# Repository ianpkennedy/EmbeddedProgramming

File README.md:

## Embedded Programming

In this repo, there are a variety of embedded programming assignments of varying difficulty using MCUs from the PIC32 family, written primarily in C with some supporting python scripts. I am particularly proud of the "Motor Control" project using nested control loops to control a electric motor over various trajectories.

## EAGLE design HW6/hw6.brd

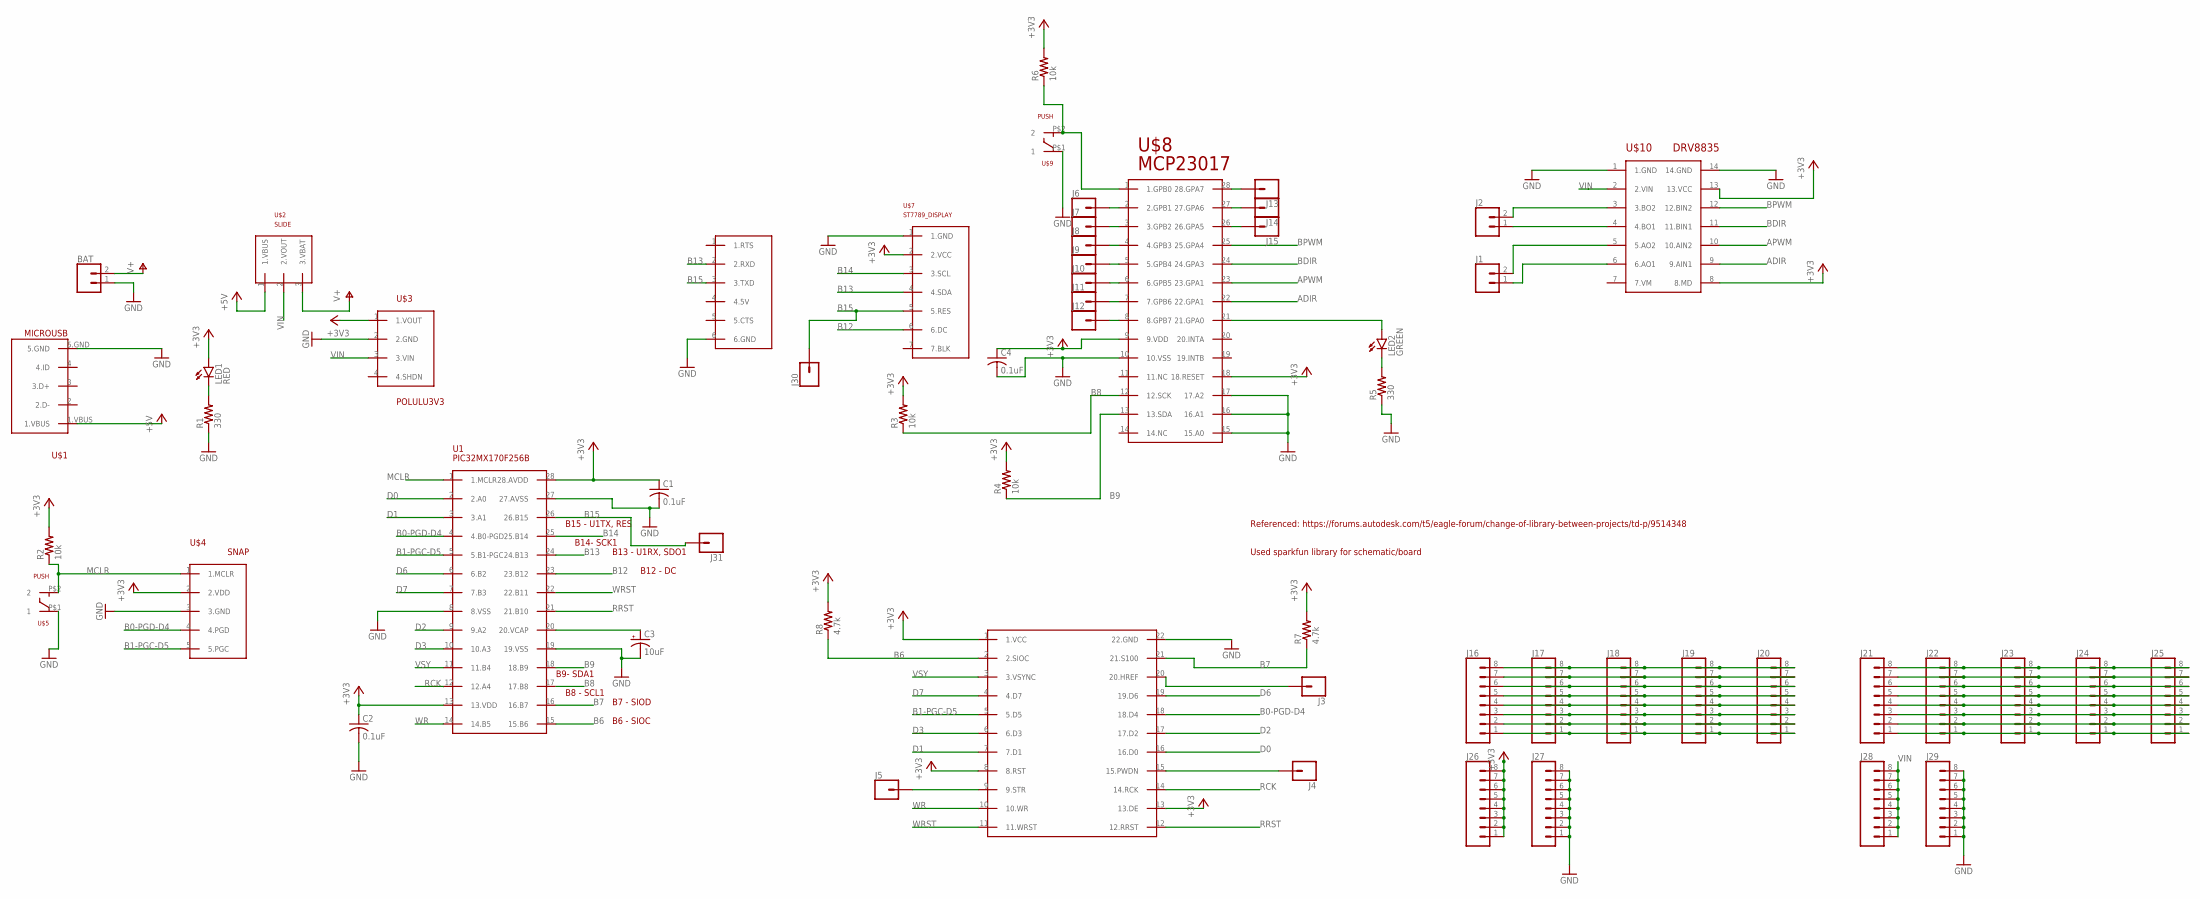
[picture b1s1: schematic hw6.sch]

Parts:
BAT: CONN_02; 1X02
C1, C2, C4: 0.1uF; C025-030X050
C3: 10uF; B45181B
J1, J2: CONN_02; 1X02
J3, J4, J5, J6, J7, J8, J9, J10, J11, J12, J13, J14, J15, J30, J31: CONN_01; 1X01
J16, J17, J18, J19, J20, J21, J22, J23, J24, J25, J26, J27, J28, J29: CONN_08"; 1X08
LED1: RED; LED3MM
LED2: GREEN; LED3MM
R1, R5: 330; 0207/10
R2, R3, R4, R6: 10k; 0207/10
R7, R8: 4.7k; 0207/10
U1: PIC32MX170F256B; DIL28-3
U$1: MICROUSB; MICROUSB1
U$2: SLIDE
U$3: POLULU3V3
U$4: SNAP
U$5, U$9: PUSH
U$6: USB2UART
U$7: ST7789_DISPLAY
U$8: MCP23017
U$10: DRV8835
U$11: OV7670_CAMERA; OV7870_CAMERA

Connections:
+3V3: C1.1, C2.1, C4.1, J26.1, J26.2, J26.3, J26.4, J26.5, J26.6, J26.7, J26.8, LED1.A, R2.2, R3.2, R4.2, R6.2, R7.2, R8.2, U1.13 (13.VDD), U1.28 (28.AVDD), U$3.1 (1.VOUT), U$4.2 (2.VDD), U$7.2 (2.VCC), U$8.9 (9.VDD), U$8.18 (18.RESET), U$10.8 (8.MD), U$10.13 (13.VCC), U$11.1 (1.VCC), U$11.8 (8.RST), U$11.13 (13.DE)
+5V: U$1.1.VBUS, U$2.1 (1.VBUS)
ADIR: U$8.22 (22.GPA1), U$10.9 (9.AIN1)
APWM: U$8.23 (23.GPA1), U$10.10 (10.AIN2)
B0-PGD-D4: U1.4 (4.B0-PGD), U$4.4 (4.PGD), U$11.18 (18.D4)
B1-PGC-D5: U1.5 (5.B1-PGC), U$4.5 (5.PGC), U$11.5 (5.D5)
B6: R8.1, U1.15 (15.B6), U$11.2 (2.SIOC)
B7: R7.1, U1.16 (16.B7), U$11.21 (21.S100)
B8: R3.1, U1.17 (17.B8), U$8.12 (12.SCK)
B9: R4.1, U1.18 (18.B9), U$8.13 (13.SDA)
B12: U1.23 (23.B12), U$7.6 (6.DC)
B13: U1.24 (24.B13), U$6.2 (2.RXD), U$7.4 (4.SDA)
B14: U1.25 (25.B14), U$7.3 (3.SCL)
B15: J30.1, J31.1, U1.26 (26.B15), U$6.3 (3.TXD), U$7.5 (5.RES)
BDIR: U$8.24 (24.GPA3), U$10.11 (11.BIN1)
BPWM: U$8.25 (25.GPA4), U$10.12 (12.BIN2)
D0: U1.2 (2.A0), U$11.16 (16.D0)
D1: U1.3 (3.A1), U$11.7 (7.D1)
D2: U1.9 (9.A2), U$11.17 (17.D2)
D3: U1.10 (10.A3), U$11.6 (6.D3)
D6: U1.6 (6.B2), U$11.19 (19.D6)
D7: U1.7 (7.B3), U$11.4 (4.D7)
GND: BAT.1, C1.2, C2.2, C3.-, C4.2, J27.1, J27.2, J27.3, J27.4, J27.5, J27.6, J27.7, J27.8, J29.1, J29.2, J29.3, J29.4, J29.5, J29.6, J29.7, J29.8, R1.1, R5.1, U1.8 (8.VSS), U1.19 (19.VSS), U1.27 (27.AVSS), U$1.5.GND, U$3.2 (2.GND), U$4.3 (3.GND), U$5.P$1 (1), U$6.6 (6.GND), U$7.1 (1.GND), U$8.10 (10.VSS), U$8.15 (15.A0), U$8.16 (16.A1), U$8.17 (17.A2), U$9.P$1 (1), U$10.1 (1.GND), U$10.14 (14.GND), U$11.22 (22.GND)
MCLR: R2.1, U1.1 (1.MCLR), U$4.1 (1.MCLR), U$5.P$2 (2)
unnamed: LED1.K (C), R1.2
unnamed: C3.+, U1.20 (20.VCAP)
unnamed: LED2.K (C), R5.2
unnamed: R6.1, U$8.1 (1.GPB0), U$9.P$2 (2)
unnamed: J2.2, U$10.3 (3.BO2)
unnamed: LED2.A, U$8.21 (21.GPA0)
unnamed: J2.1, U$10.4 (4.BO1)
unnamed: J1.2, U$10.5 (5.AO2)
unnamed: J1.1, U$10.6 (6.AO1)
unnamed: J5.1, U$11.9 (9.STR)
unnamed: J4.1, U$11.15 (15.PWDN)
unnamed: J3.1, U$11.20 (20.HREF)
unnamed: J6.1, U$8.2 (2.GPB1)
unnamed: J7.1, U$8.3 (3.GPB2)
unnamed: J8.1, U$8.4 (4.GPB3)
unnamed: J9.1, U$8.5 (5.GPB4)
unnamed: J10.1, U$8.6 (6.GPB5)
unnamed: J11.1, U$8.7 (7.GPB6)
unnamed: J12.1, U$8.8 (8.GPB7)
unnamed: J15.1, U$8.26 (26.GPA5)
unnamed: J14.1, U$8.27 (27.GPA6)
unnamed: J13.1, U$8.28 (28.GPA7)
unnamed: J16.8, J17.8, J18.8, J19.8, J20.8
unnamed: J16.7, J17.7, J18.7, J19.7, J20.7
unnamed: J16.6, J17.6, J18.6, J19.6, J20.6
unnamed: J16.5, J17.5, J18.5, J19.5, J20.5
unnamed: J16.4, J17.4, J18.4, J19.4, J20.4
unnamed: J16.3, J17.3, J18.3, J19.3, J20.3
unnamed: J16.2, J17.2, J18.2, J19.2, J20.2
unnamed: J16.1, J17.1, J18.1, J19.1, J20.1
unnamed: J21.1, J22.1, J23.1, J24.1, J25.1
unnamed: J21.2, J22.2, J23.2, J24.2, J25.2
unnamed: J21.3, J22.3, J23.3, J24.3, J25.3
unnamed: J21.4, J22.4, J23.4, J24.4, J25.4
unnamed: J21.5, J22.5, J23.5, J24.5, J25.5
unnamed: J21.6, J22.6, J23.6, J24.6, J25.6
unnamed: J21.7, J22.7, J23.7, J24.7, J25.7
unnamed: J21.8, J22.8, J23.8, J24.8, J25.8
RCK: U1.12 (12.A4), U$11.14 (14.RCK)
RRST: U1.21 (21.B10), U$11.12 (12.RRST)
V+: BAT.2, U$2.3 (3.VBAT)
VIN: J28.1, J28.2, J28.3, J28.4, J28.5, J28.6, J28.7, J28.8, U$2.2 (2.VOUT), U$3.3 (3.VIN), U$10.2 (2.VIN)
VSY: U1.11 (11.B4), U$11.3 (3.VSYNC)
WR: U1.14 (14.B5), U$11.10 (10.WR)
WRST: U1.22 (22.B11), U$11.11 (11.WRST)

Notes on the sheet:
B6 - SIOC
B7 - SIOD
B8 - SCL1
B9- SDA1
B12 - DC
B13 - U1RX, SDO1
B14- SCK1
B15 - U1TX, RES
Referenced: https://forums.autodesk.com/t5/eagle-forum/change-of-library-between-projects/td-p/9514348
Used sparkfun library for schematic/board

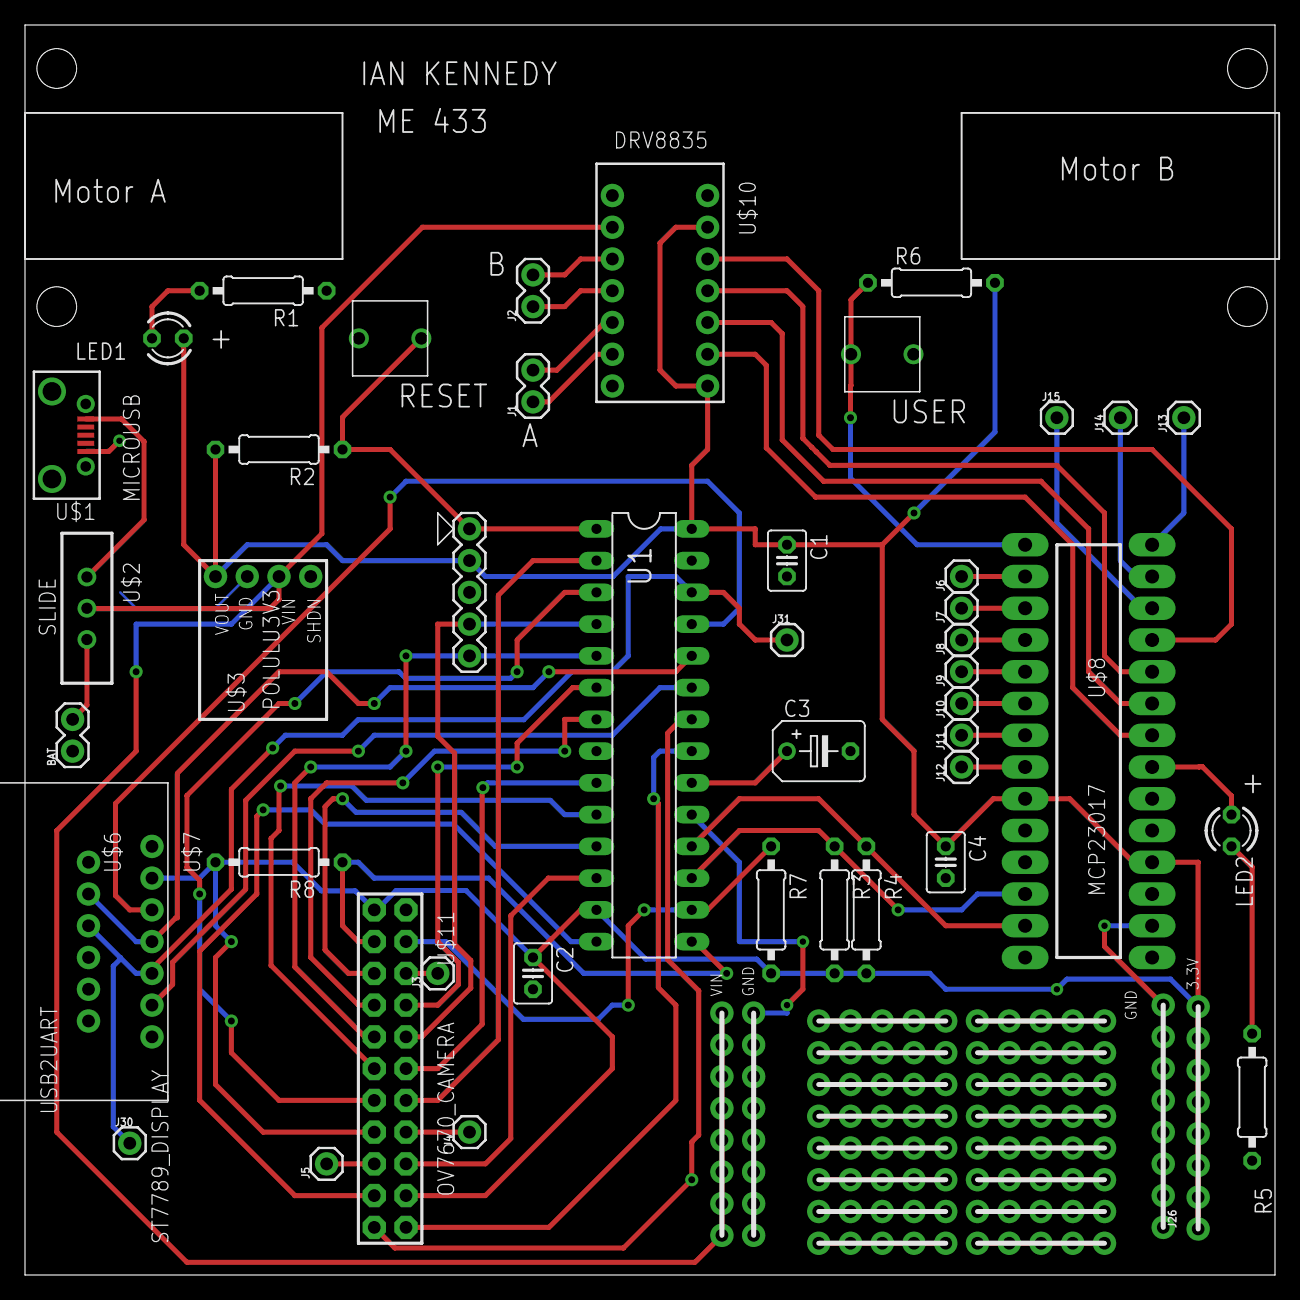
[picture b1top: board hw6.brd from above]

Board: 2 copper layers, 100.0 x 100.0 mm, 58 parts (0 on the bottom side), 69 nets.

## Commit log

2021-12-14 adding embedded design
2021-12-14 restructuring
2021-12-14 updating readme
2021-12-14 adding readme
2021-12-14 updating lcd display
2021-12-14 correcting
2021-12-14 adding gif
2021-12-14 Updating image
2021-12-14 udpate
2021-12-14 committing gif
2021-12-14 updating with pics
2021-12-14 updating demo
2021-12-15 Updating
2021-12-21 Updating UART
2021-12-22 signal processing
2021-12-22 servo
2021-12-22 neopixel
2021-12-22 motor
2021-12-22 basic
2021-12-22 intro
